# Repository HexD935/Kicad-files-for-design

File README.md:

This is a repository for the design files of Jonathan Cohn and Simamkele Shologu's EEE3088F power subsystem.
_______________________________________________________________________________________________________
Problem Description:
_______________________________________________________________________________________________________
The goal is to create a robot that can solve a maze without external interference. This robot is known
as a Micro-Mouse(MM) and has become a somewhat infamous engineering example, with many trying
to make them solve the mazes faster and faster. A typical MM includes 4 major subsystems: power,
sensing, processor, and motherboard. This is being made for a university assignment where speed
does not matter. The specific part of the robot that has been assigned is the power subsystem which
will communicate with the MM’s microcontroller(uM) and various other parts to provide the required
currents and voltages to the required systems. As such the sensing, processor, and motherboard have
already been designed. The power system will need to interface with the motherboard that will connect
the rest of the subsystems and power the entire MM.
_______________________________________________________________________________________________________
Files Included:
_______________________________________________________________________________________________________
The KICAD design files are included in this repo which is the schematic and PCB files. There are also the 
history of edits et. 
_______________________________________________________________________________________________________
Usage:
_______________________________________________________________________________________________________
These files can be downloaded as a ZIP file which will need to be extracted into a local file. 
                       !!!!!THIS CAN ONLY BE RUN IN KICAD 9!!!!!!

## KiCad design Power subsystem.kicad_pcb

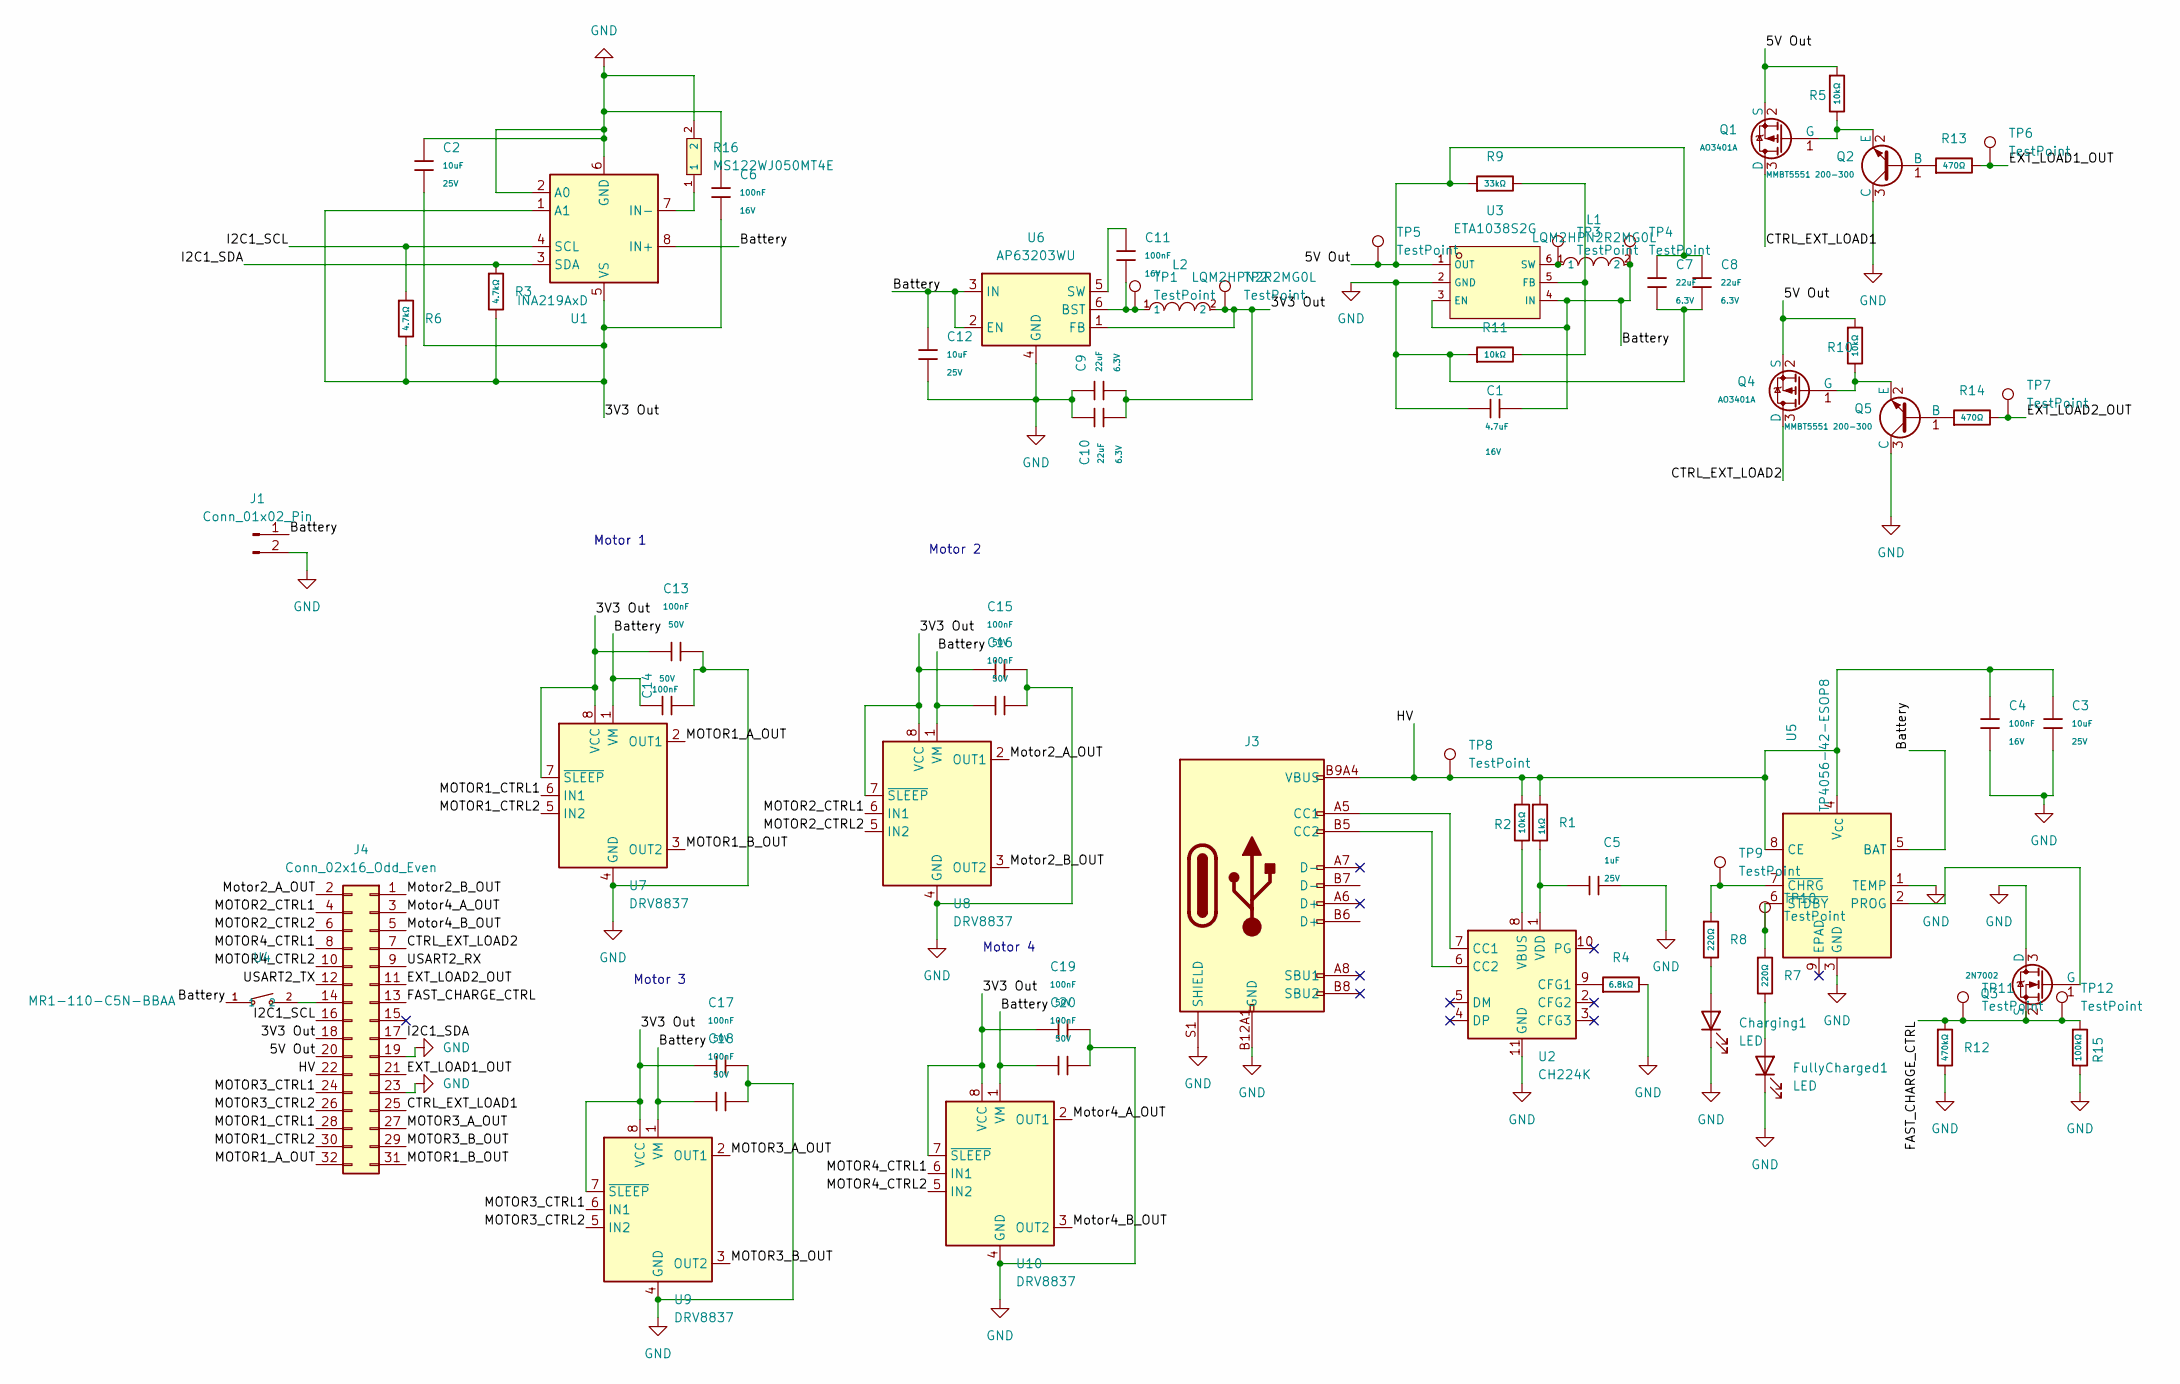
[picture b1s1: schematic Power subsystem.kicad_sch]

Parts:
C1: 4.7uF; C_0603; Voltage Rated 16V; Tolerance ±10%; Part CL10A475KO8NNNC; LCSC C19666
C2, C3, C12: 10uF; C_0805; Voltage Rated 25V; Tolerance ±10%; Part CL21A106KAYNNNE; LCSC C15850
C4, C6, C11: 100nF; C_0402; Voltage Rated 16V; Tolerance ±10%; Part CL05B104KO5NNNC; LCSC C1525
C5: 1uF; C_0402; Voltage Rated 25V; Tolerance ±10%; Part CL05A105KA5NQNC; LCSC C52923
C7, C8, C9, C10: 22uF; C_0603; Voltage Rated 6.3V; Tolerance ±20%; Part CL10A226MQ8NRNC; LCSC C59461
C13, C14, C15, C16, C17, C18, C19, C20: 100nF; C_0603; Voltage Rated 50V; Tolerance ±10%; Part CC0603KRX7R9BB104; LCSC C14663
Charging1: LED; LED_0805_2012Metric_Pad1.15x1.40mm_HandSolder
FullyCharged1: LED; LED_1206_3216Metric_Pad1.42x1.75mm_HandSolder
J1: Conn_01x02_Pin; JST_PH_B2B-PH-K_1x02_P2.00mm_Vertical
J3: Connector, USB-TYPE-C-16P; TYPE-C-SMD_HX-TYPE-C-16PIN; LCSC C2927039
J4: Conn_02x16_Odd_Even; PinHeader_2x16_P2.54mm_Vertical
L1, L2: LQM2HPN2R2MG0L; L1008; LCSC C86092
Q1, Q4: AO3401A; Q_SOT-23; Part AO3401A; LCSC C15127
Q2, Q5: MMBT5551 200-300; Q_SOT-23; Part MMBT5551(RANGE:200-300); LCSC C2145
Q3: 2N7002; Q_SOT-23; Part 2N7002; LCSC C8545
R1: 1kΩ; R_0603; Overload Voltage (Max) 75V; Tolerance ±1%; Part 0603WAF1001T5E; LCSC C21190
R2, R5, R10, R11: 10kΩ; R_0603; Overload Voltage (Max) 75V; Tolerance ±1%; Part 0603WAF1002T5E; LCSC C25804
R3, R6: 4.7kΩ; R_0805; Overload Voltage (Max) 150V; Tolerance ±1%; Part 0805W8F4701T5E; LCSC C17673
R4: 6.8kΩ; R_0603; Overload Voltage (Max) 75V; Tolerance ±1%; Part 0603WAF6801T5E; LCSC C23212
R7, R8: 220Ω; R_0603; Overload Voltage (Max) 75V; Tolerance ±1%; Part 0603WAF2200T5E; LCSC C22962
R9: 33kΩ; R_0603; Overload Voltage (Max) 75V; Tolerance ±1%; Part 0603WAF3302T5E; LCSC C4216
R12: 470kΩ; R_0805; Overload Voltage (Max) 150V; Tolerance ±1%; Part 0805W8F4703T5E; LCSC C17709
R13, R14: 470Ω; R_0603; Overload Voltage (Max) 75V; Tolerance ±1%; Part 0603WAF4700T5E; LCSC C23179
R15: 100kΩ; R_0402; Overload Voltage (Max) 50V; Tolerance ±1%; Part 0402WGF1003TCE; LCSC C25741
R16: MS122WJ050MT4E; R2512; LCSC C49483
TP1, TP2, TP3, TP4, TP5, TP6, TP7, TP8, TP9, TP10, TP11, TP12: TestPoint; TestPoint_Pad_2.0x2.0mm
U1: INA219AxD; SOIC-8_3.9x4.9mm_P1.27mm
U2: CH224K; SSOP-10-1EP_3.9x4.9mm_P1mm_EP2.1x3.3mm
U3: ETA1038S2G; SOT-23-6_L2.9-W1.6-P0.95-LS2.8-BR; LCSC C7465552
U4: MR1-110-C5N-BBAA; SW-TH_MR1-110-C5N-BBAA; LCSC C268221
U5: TP4056-42-ESOP8; SOIC-8-1EP_3.9x4.9mm_P1.27mm_EP2.41x3.3mm_ThermalVias
U6: AP63203WU; TSOT-23-6
U7, U8, U9, U10: DRV8837; WSON-8-1EP_2x2mm_P0.5mm_EP0.9x1.6mm

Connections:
/3V3 Out: C2.2, C6.2, C9.2, C10.2, C13.1, C15.1, C17.1, C19.1, J4.18, L2.2, R3.2, R6.2, TP2.1, U1.1 (A1), U1.5 (VS), U6.1 (FB), U7.7 (~SLEEP), U7.8 (VCC), U8.7 (~SLEEP), U8.8 (VCC), U9.7 (~SLEEP), U9.8 (VCC), U10.7 (~SLEEP), U10.8 (VCC)
/5V Out: C7.1, C8.1, J4.20, Q1.2 (S), Q4.2 (S), R5.1, R9.1, R10.1, TP5.1, U3.1 (OUT)
/Battery: C1.2, C12.1, C14.1, C16.1, C18.1, C20.1, J1.1, L1.2, TP4.1, U1.8 (IN+), U3.3 (EN), U3.4 (IN), U4.1, U5.5 (BAT), U6.2 (EN), U6.3 (IN), U7.1 (VM), U8.1 (VM), U9.1 (VM), U10.1 (VM)
/CTRL_EXT_LOAD1: J4.25
/CTRL_EXT_LOAD1: Q1.3 (D)
/CTRL_EXT_LOAD2: J4.7, Q4.3 (D)
/EXT_LOAD1_OUT: J4.21, R13.2, TP6.1
/EXT_LOAD2_OUT: J4.11, R14.2, TP7.1
/FAST_CHARGE_CTRL: J4.13
/FAST_CHARGE_CTRL: Q3.2 (S), R12.1, R15.1, TP11.1, TP12.1
/HV: C3.1, C4.1, J3.A9B4 (VBUS), J3.B9A4 (VBUS), J4.22, R1.1, R2.1, TP8.1, U5.4 (V_{CC}), U5.8 (CE)
/I2C1_SCL: J4.16, R6.1, U1.4 (SCL)
/I2C1_SDA: J4.17, R3.1, U1.3 (SDA)
/MOTOR1_A_OUT: J4.32, U7.2 (OUT1)
/MOTOR1_B_OUT: J4.31, U7.3 (OUT2)
/MOTOR1_CTRL1: J4.28, U7.6 (IN1)
/MOTOR1_CTRL2: J4.30, U7.5 (IN2)
/MOTOR2_CTRL1: J4.4, U8.6 (IN1)
/MOTOR2_CTRL2: J4.6, U8.5 (IN2)
/MOTOR3_A_OUT: J4.27, U9.2 (OUT1)
/MOTOR3_B_OUT: J4.29, U9.3 (OUT2)
/MOTOR3_CTRL1: J4.24, U9.6 (IN1)
/MOTOR3_CTRL2: J4.26, U9.5 (IN2)
/MOTOR4_CTRL1: J4.8, U10.6 (IN1)
/MOTOR4_CTRL2: J4.10, U10.5 (IN2)
/Motor2_A_OUT: J4.2, U8.2 (OUT1)
/Motor2_B_OUT: J4.1, U8.3 (OUT2)
/Motor4_A_OUT: J4.3, U10.2 (OUT1)
/Motor4_B_OUT: J4.5, U10.3 (OUT2)
/USART2_RX: J4.9
/USART2_TX: J4.12
GND: C1.1, C2.1, C3.2, C4.2, C5.2, C6.1, C7.2, C8.2, C9.1, C10.1, C12.2, C13.2, C14.2, C15.2, C16.2, C17.2, C18.2, C19.2, C20.2, Charging1.1 (K), FullyCharged1.1 (K), J1.2, J3.A12B1 (GND), J3.B12A1 (GND), J3.S1 (SHIELD), J4.19, J4.23, Q2.3 (C), Q3.3 (D), Q5.3 (C), R4.2, R11.1, R12.2, R15.2, R16.2, U1.2 (A0), U1.6 (GND), U2.11 (GND), U3.2 (GND), U5.1 (TEMP), U5.3 (GND), U6.4 (GND), U7.4 (GND), U7.9 (GND), U8.4 (GND), U8.9 (GND), U9.4 (GND), U9.9 (GND), U10.4 (GND), U10.9 (GND)
unnamed: Charging1.2 (A), R8.2
unnamed: FullyCharged1.2 (A), R7.2
unnamed: J3.A5 (CC1), U2.7 (CC1)
unnamed: J3.B5 (CC2), U2.6 (CC2)
unnamed: J4.14, U4.2
unnamed: Q1.1 (G), Q2.2 (E), R5.2
unnamed: Q2.1 (B), R13.1
unnamed: Q3.1 (G), U5.2 (PROG)
unnamed: Q4.1 (G), Q5.2 (E), R10.2
unnamed: Q5.1 (B), R14.1
unnamed: R16.1, U1.7 (IN-)
unnamed: R4.1, U2.9 (CFG1)
unnamed: R2.2, U2.8 (VBUS)
unnamed: C5.1, R1.2, U2.1 (VDD)
unnamed: R9.2, R11.2, U3.5 (FB)
unnamed: L1.1, TP3.1, U3.6 (SW)
unnamed: R8.1, TP9.1, U5.7 (~CHRG)
unnamed: R7.1, TP10.1, U5.6 (~STDBY)
unnamed: C11.2, L2.1, TP1.1, U6.6 (BST)
unnamed: C11.1, U6.5 (SW)

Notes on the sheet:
Motor 1
Motor 2
Motor 4
Motor 3

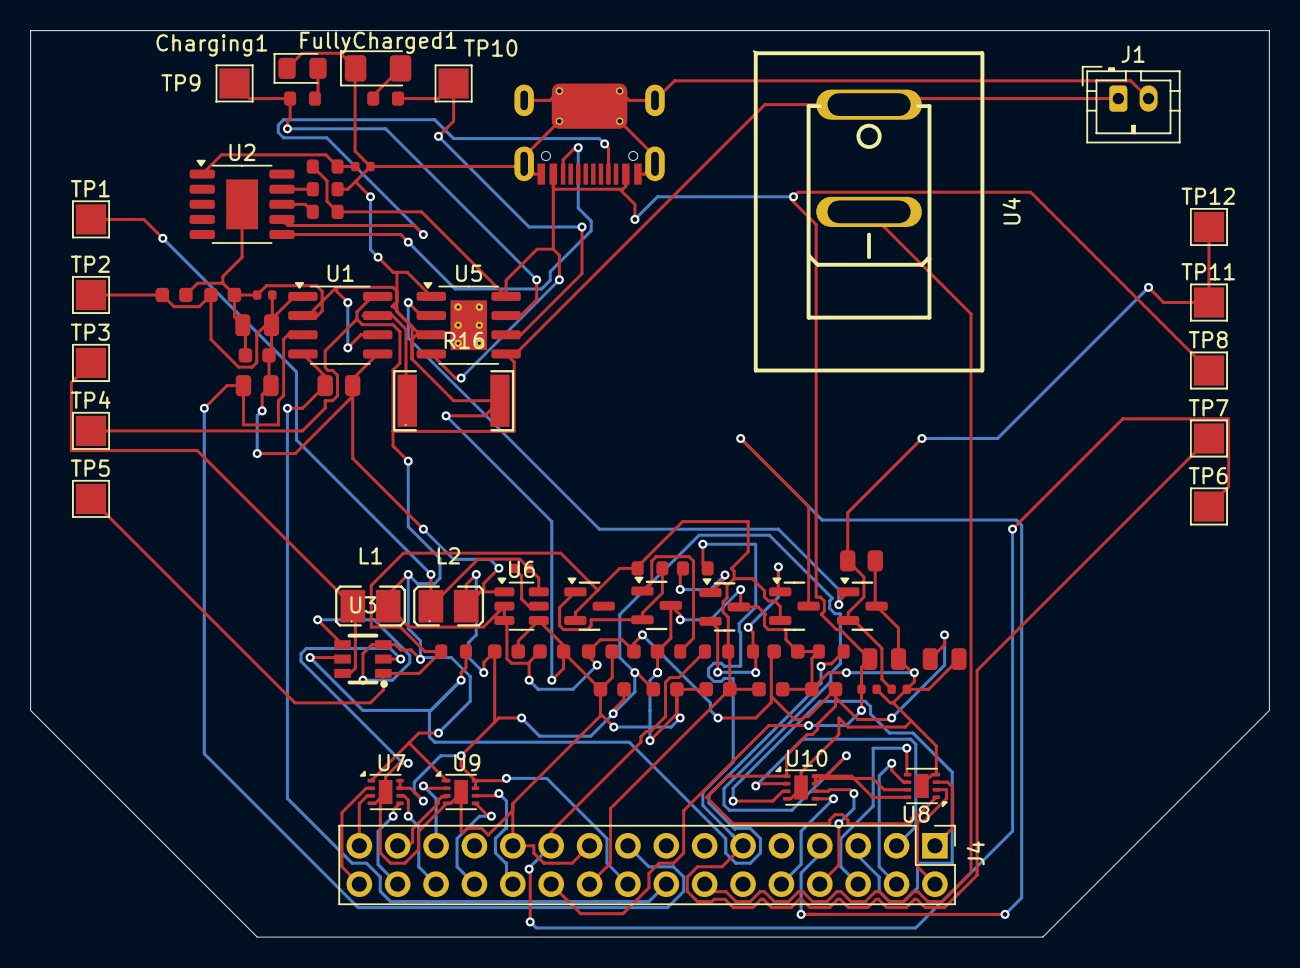
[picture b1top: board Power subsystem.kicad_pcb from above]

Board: 2 copper layers, 82.0 x 60.0 mm, 70 parts (0 on the bottom side), 47 nets.
